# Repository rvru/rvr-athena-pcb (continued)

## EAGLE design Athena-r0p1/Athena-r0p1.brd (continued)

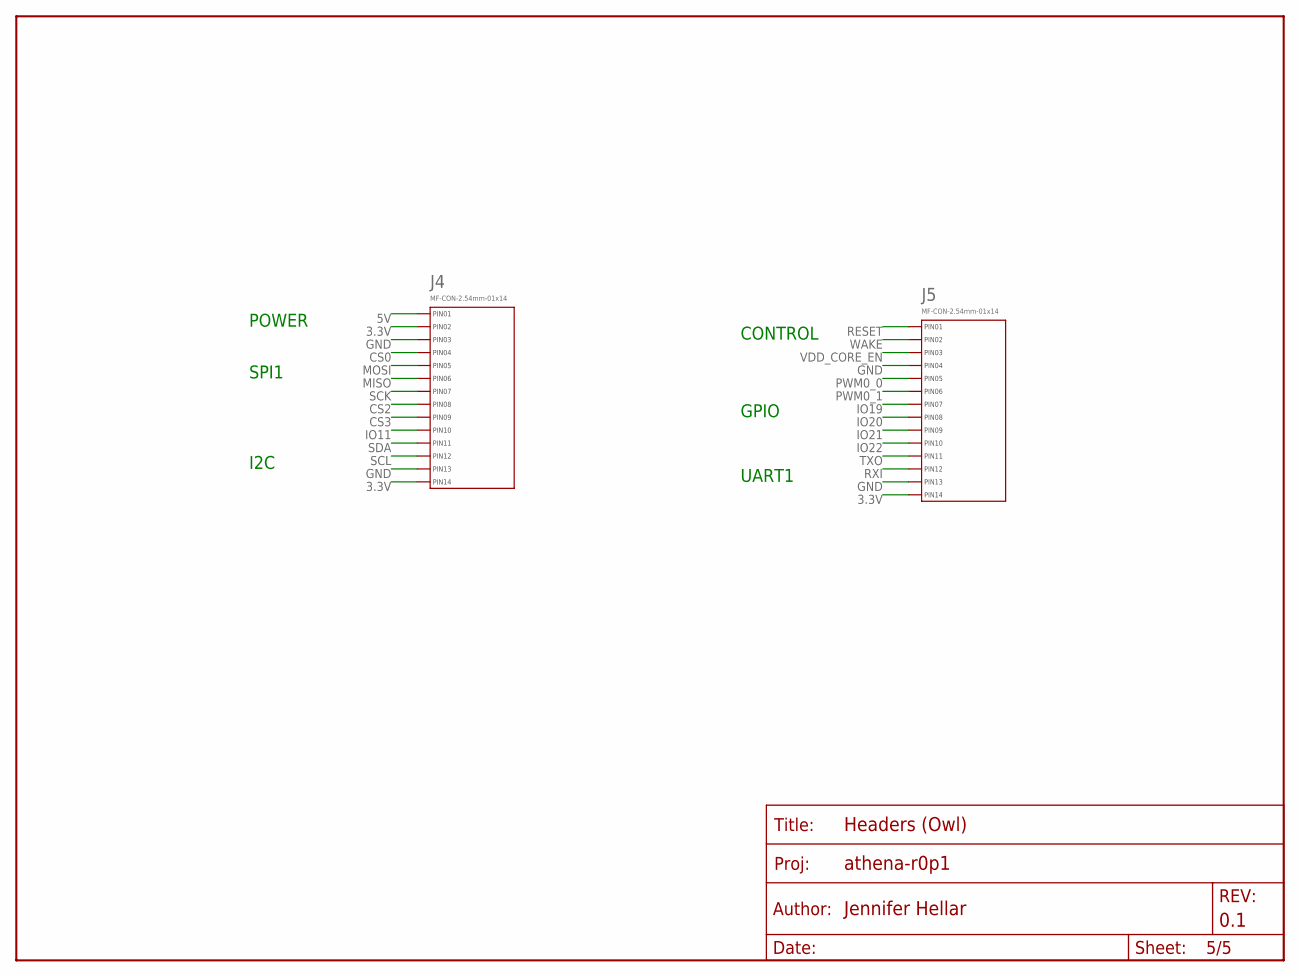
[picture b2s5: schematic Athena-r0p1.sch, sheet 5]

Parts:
FRAME4: FRAME-LETTER; SPARKFUN-AESTHETICS_CREATIVE_COMMONS
J4, J5: MF-CON-2.54mm-01x14; PTH_2.54MM_01X14

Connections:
3.3V: J4.P$2 (PIN2), J4.P$14 (PIN14), J5.P$14 (PIN14); also elsewhere on the board
5V: J4.P$1 (PIN1); also elsewhere on the board
CS0: J4.P$4 (PIN4); also elsewhere on the board
CS2: J4.P$8 (PIN8); also elsewhere on the board
CS3: J4.P$9 (PIN9); also elsewhere on the board
GND: J4.P$3 (PIN3), J4.P$13 (PIN13), J5.P$4 (PIN4), J5.P$13 (PIN13); also elsewhere on the board
IO11: J4.P$10 (PIN10); also elsewhere on the board
IO19: J5.P$7 (PIN7); also elsewhere on the board
IO20: J5.P$8 (PIN8); also elsewhere on the board
IO21: J5.P$9 (PIN9); also elsewhere on the board
IO22: J5.P$10 (PIN10); also elsewhere on the board
MISO: J4.P$6 (PIN6); also elsewhere on the board
MOSI: J4.P$5 (PIN5); also elsewhere on the board
PWM0_0: J5.P$5 (PIN5); also elsewhere on the board
PWM0_1: J5.P$6 (PIN6); also elsewhere on the board
RESET: J5.P$1 (PIN1); also elsewhere on the board
RXI: J5.P$12 (PIN12); also elsewhere on the board
SCK: J4.P$7 (PIN7); also elsewhere on the board
SCL: J4.P$12 (PIN12); also elsewhere on the board
SDA: J4.P$11 (PIN11); also elsewhere on the board
TXO: J5.P$11 (PIN11); also elsewhere on the board
VDD_CORE_EN: J5.P$3 (PIN3); also elsewhere on the board
WAKE: J5.P$2 (PIN2); also elsewhere on the board

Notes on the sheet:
SPI1
I2C
UART1
GPIO
CONTROL
POWER

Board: 4 copper layers, 78 parts (0 on the bottom side), 68 nets, no tracks yet.

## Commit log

2021-03-20 SiFive Hifive Rev. B BOM/Sch/Brd pdfs and altium files. FE310-G002 Datasheet and Manual.
2021-05-21 Added Sparkfun RED-V reference design, including BOM and library
2021-05-21 Created initial Athena library from parts imported from Sparkfun Red-V and Adafruit Feather designs. Updated README. Added Adafruit reference design.
2021-05-26 Initial work on the power supply portion of the schematic
2021-05-26 Initial work on the MCU portion of the schematic incl. oscillators and flash
2021-05-26 Initial work on the USB-JTAG portion of Nest. Added PWR/JTAG header to separate Owl and Nest. Pdf of RedBoard schematic reference added for ease of viewing
2021-06-01 Athena Rev. 0.1 Schematic complete.
    1. Switched out oscillators to match the parts used in HiFive
    2. Cleaned and commented the schematics
    3. Completed the header pinout
    4. Removed unused parts from the library
    5. Added datasheets for all non-passives
2021-06-05 Started on the board design. IC and header placement, GND and 3.3V layer polygon pours. The long I/O headers are limiting board size. Switch to short double column headers?
2021-06-28 Initial work on addressing Erik's feedback of r0p1
2021-06-28 Continued work on addressing Erik's comments, specifically, removing the NCP1117. Also changed out the TVS diodes to the devices in the HiFive design.
2021-08-05 Implementing changes suggested by Erik and Ashish during July schematic review
2021-08-06 Finished updates based on design review feedback. Added mounting holes and chassis GND. Converted all passives to 0402. Renumbered all parts. Added cover page. Replaced SiTime oscillator with std foo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
2021-08-06 New library includes all parts for Athena r1p0 (including from other libraries).
2021-08-17 First pass at Athena layout. Passes all DRC except for issues with the USB port pads (which is a MF housepart)
2022-05-19 Updated design
    Removed off-board debug header
2022-06-06 Athena A1 initial design pre-review
2022-07-11 Updates post-review in progress
    Sch: added power switch, improved symbols, added cap on Wake, added 0Ohm res to crystal, mikro gpio instead of wake/reset
    Brd: moved tag connect to top, added clearance for mikro click brds, routed new switch, etc.
    Todo: silkscreen cleanup and checking
2022-07-25 Finished updates post-review
2022-07-25 Moved pours outside dimension
2022-10-01 Athena A1 final
    Minor board cleanup
2022-10-01 Athena A1 final (for real, now)
    Fixed some text that got moved over pours and one trace with a weird angle
2022-10-01 updated .pdf
